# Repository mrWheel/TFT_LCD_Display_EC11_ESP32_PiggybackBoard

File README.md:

# TFT-LCD-Display-EC11 Piggy Back Board

## SoC
This Piggy Back Board uses an **ESP32-S3 SoC**

The board revision is Rev 3.1

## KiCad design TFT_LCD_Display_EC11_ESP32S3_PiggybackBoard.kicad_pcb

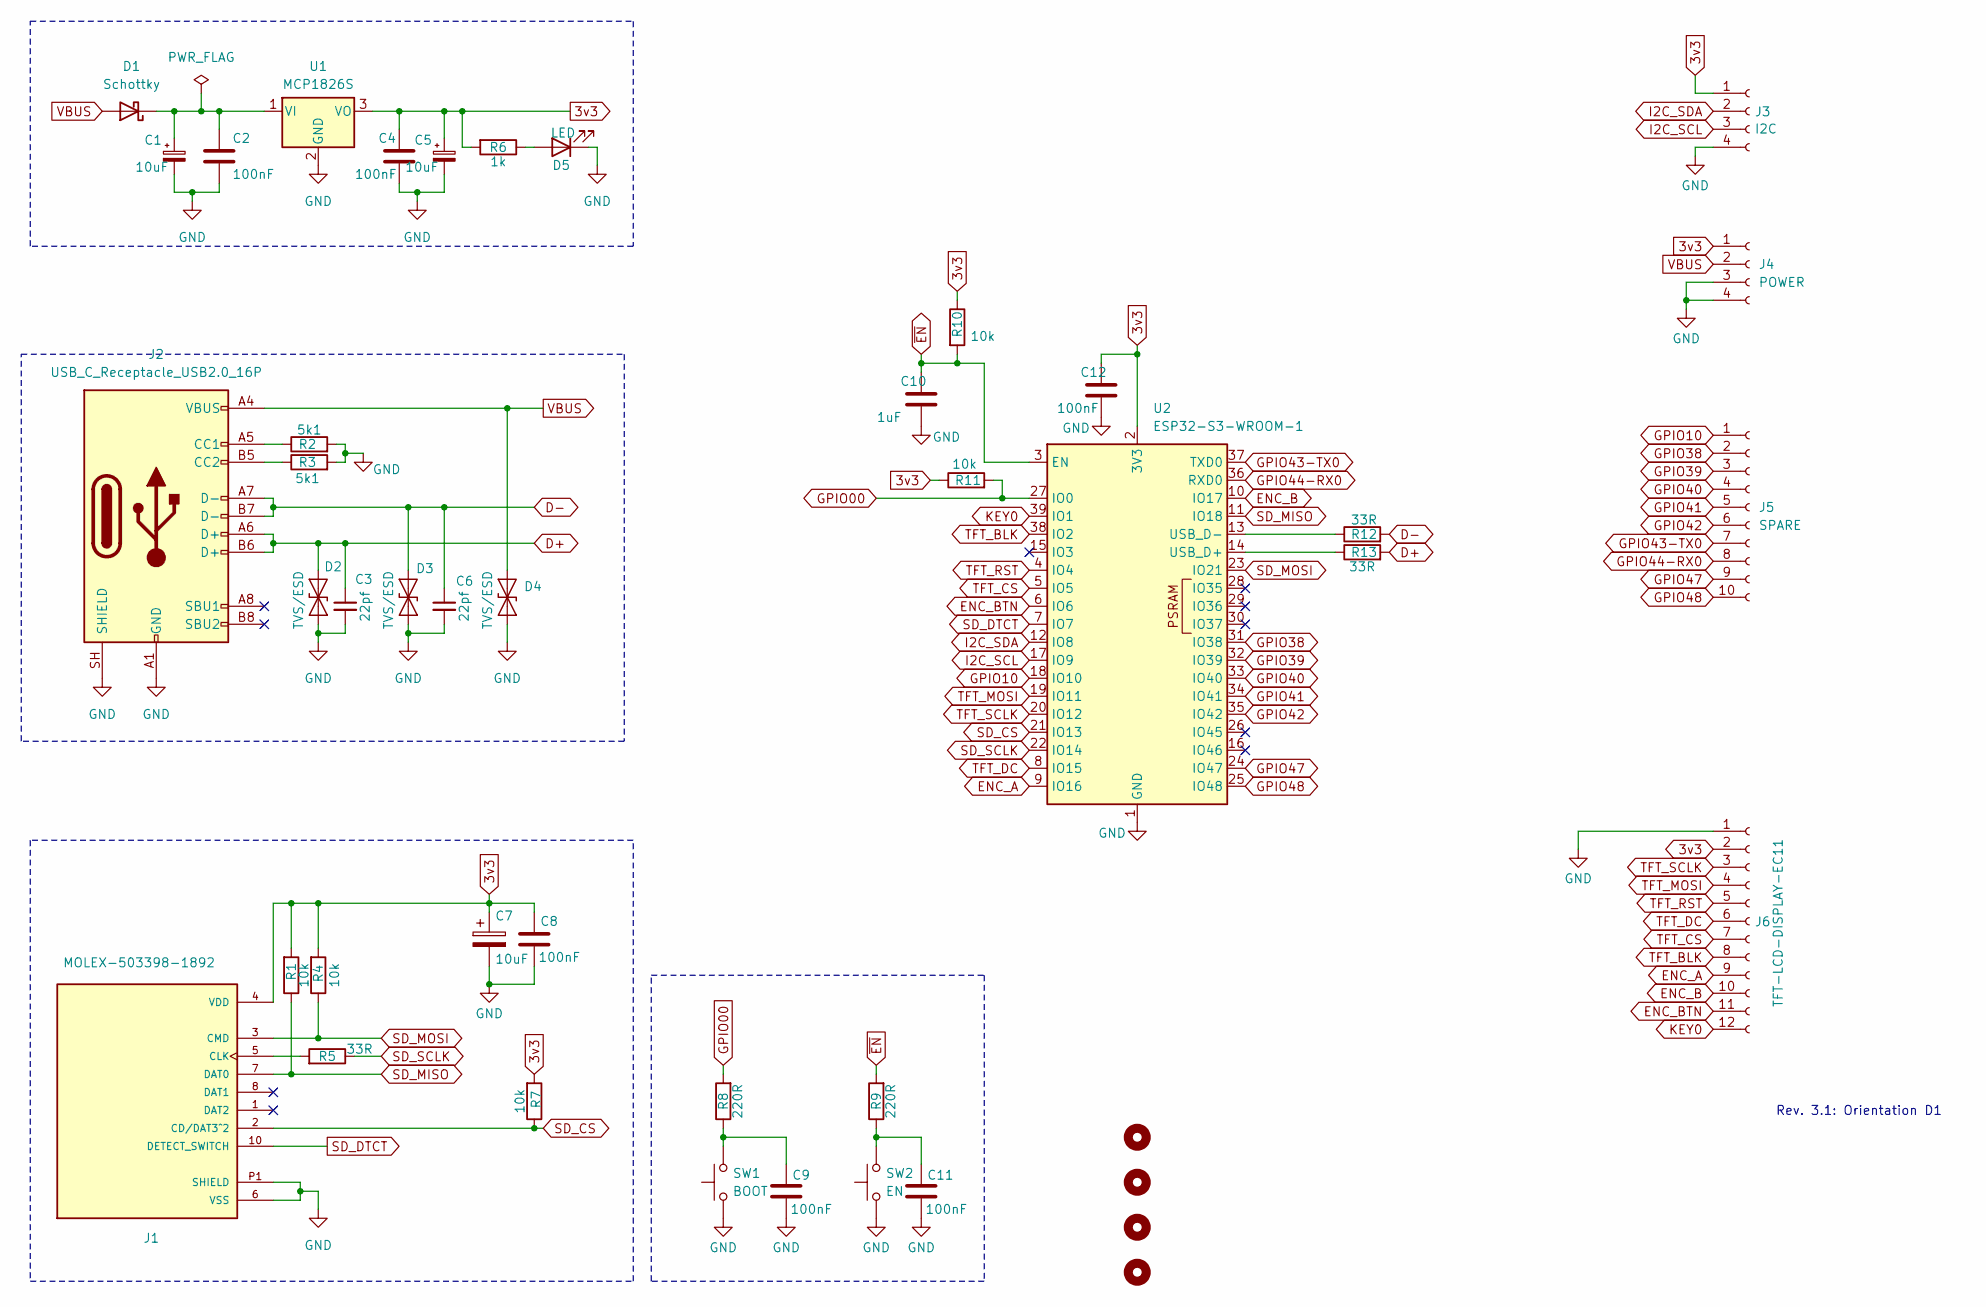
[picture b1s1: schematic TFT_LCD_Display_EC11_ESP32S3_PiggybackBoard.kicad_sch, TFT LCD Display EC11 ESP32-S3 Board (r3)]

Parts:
C1, C5: 10uF; CP_EIA-3216-18_Kemet-A_HandSolder
C2, C4, C8, C9, C11, C12: 100nF; C_1206_3216Metric_Pad1.33x1.80mm_HandSolder
C3, C6: 22pf; C_1206_3216Metric_Pad1.33x1.80mm_HandSolder
C7: 10uF; CP_EIA-7343-31_Kemet-D_HandSolder
C10: 1uF; C_1206_3216Metric_Pad1.33x1.80mm_HandSolder
D1: Schottky; D_SMA_Handsoldering
D2, D3, D4: TVS/ESD; D_SOD-123F
D5: LED; LED_1206_3216Metric_Pad1.42x1.75mm_HandSolder
H1, H2, H3, H4: MountingHole; MountingHole_3.2mm_M3_DIN965_Pad
J1: MOLEX-503398-1892; MOLEX_503398-1892_mod; PARTREV 0
J2: USB_C_Receptacle_USB2.0_16P; USB_C_Receptacle_GCT_USB4085
J3: I2C; PinSocket_1x04_P2.54mm_Vertical
J4: POWER; PinSocket_1x04_P2.54mm_Vertical
J5: SPARE; PinSocket_1x10_P2.54mm_Vertical
J6: TFT-LCD-DISPLAY-EC11; PinHeader_1x12_P2.54mm_Vertical
R1, R4, R7, R10, R11: 10k; R_1206_3216Metric_Pad1.30x1.75mm_HandSolder
R2, R3: 5k1; R_1206_3216Metric_Pad1.30x1.75mm_HandSolder
R5, R12, R13: 33R; R_1206_3216Metric_Pad1.30x1.75mm_HandSolder
R6: 1k; R_1206_3216Metric_Pad1.30x1.75mm_HandSolder
R8, R9: 220R; R_1206_3216Metric_Pad1.30x1.75mm_HandSolder
SW1: BOOT; SW_SPST_FSMSM
SW2: EN; SW_SPST_FSMSM
U1: MCP1826S; SOT-223-3_TabPin2
U2: ESP32-S3-WROOM-1

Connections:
3v3: C4.1, C5.1, C7.1, C8.1, C12.1, J1.4 (VDD), J3.1, J4.1, J6.2, R1.2, R4.2, R6.2, R7.2, R10.1, R11.1, U1.3 (VO), U2.2 (3V3)
D+: C3.1, D2.2 (A2), J2.A6 (D+), J2.B6 (D+), R13.2
D-: C6.1, D3.2 (A2), J2.A7 (D-), J2.B7 (D-), R12.2
ENC_A: J6.9, U2.9 (IO16)
ENC_B: J6.10, U2.10 (IO17)
ENC_BTN: J6.11, U2.6 (IO6)
GND: C1.2, C2.2, C3.2, C4.2, C5.2, C6.2, C7.2, C8.2, C9.2, C10.2, C11.2, C12.2, D2.1 (A1), D3.1 (A1), D4.1 (A1), D5.1 (K), J1.6 (VSS), J1.9 (VSS), J1.P1 (SHIELD), J1.P2 (SHIELD), J1.P3 (SHIELD), J1.P4 (SHIELD), J2.A1 (GND), J2.A12 (GND), J2.B1 (GND), J2.B12 (GND), J2.SH (SHIELD), J3.4, J4.3, J4.4, J6.1, R2.2, R3.2, SW1.1, SW2.1, U1.2 (GND), U2.1 (GND), U2.40 (GND), U2.41 (GND)
GPIO00: R8.2, R11.2, U2.27 (IO0)
GPIO10: J5.1, U2.18 (IO10)
GPIO38: J5.2, U2.31 (IO38)
GPIO39: J5.3, U2.32 (IO39)
GPIO40: J5.4, U2.33 (IO40)
GPIO41: J5.5, U2.34 (IO41)
GPIO42: J5.6, U2.35 (IO42)
GPIO43-TX0: J5.7, U2.37 (TXD0)
GPIO44-RX0: J5.8, U2.36 (RXD0)
GPIO47: J5.9, U2.24 (IO47)
GPIO48: J5.10, U2.25 (IO48)
I2C_SCL: J3.3, U2.17 (IO9)
I2C_SDA: J3.2, U2.12 (IO8)
KEY0: J6.12, U2.39 (IO1)
unnamed: C9.1, R8.1, SW1.2
unnamed: C11.1, R9.1, SW2.2
unnamed: C1.1, C2.1, D1.1 (K), U1.1 (VI)
unnamed: D5.2 (A), R6.1
unnamed: J1.5 (CLK), R5.2
unnamed: J2.A5 (CC1), R2.1
unnamed: J2.B5 (CC2), R3.1
unnamed: R13.1, U2.14 (USB_D+)
unnamed: R12.1, U2.13 (USB_D-)
SD_CS: J1.2 (CD/DAT3^2), R7.1, U2.21 (IO13)
SD_DTCT: J1.10 (DETECT_SWITCH), U2.7 (IO7)
SD_MISO: J1.7 (DAT0), R1.1, U2.11 (IO18)
SD_MOSI: J1.3 (CMD), R4.1, U2.23 (IO21)
SD_SCLK: R5.1, U2.22 (IO14)
TFT_BLK: J6.8, U2.38 (IO2)
TFT_CS: J6.7, U2.5 (IO5)
TFT_DC: J6.6, U2.8 (IO15)
TFT_MOSI: J6.4, U2.19 (IO11)
TFT_RST: J6.5, U2.4 (IO4)
TFT_SCLK: J6.3, U2.20 (IO12)
VBUS: D1.2 (A), D4.2 (A2), J2.A4 (VBUS), J2.A9 (VBUS), J2.B4 (VBUS), J2.B9 (VBUS), J4.2
~EN: C10.1, R9.2, R10.2, U2.3 (EN)

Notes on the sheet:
Rev. 3.1: Orientation D1

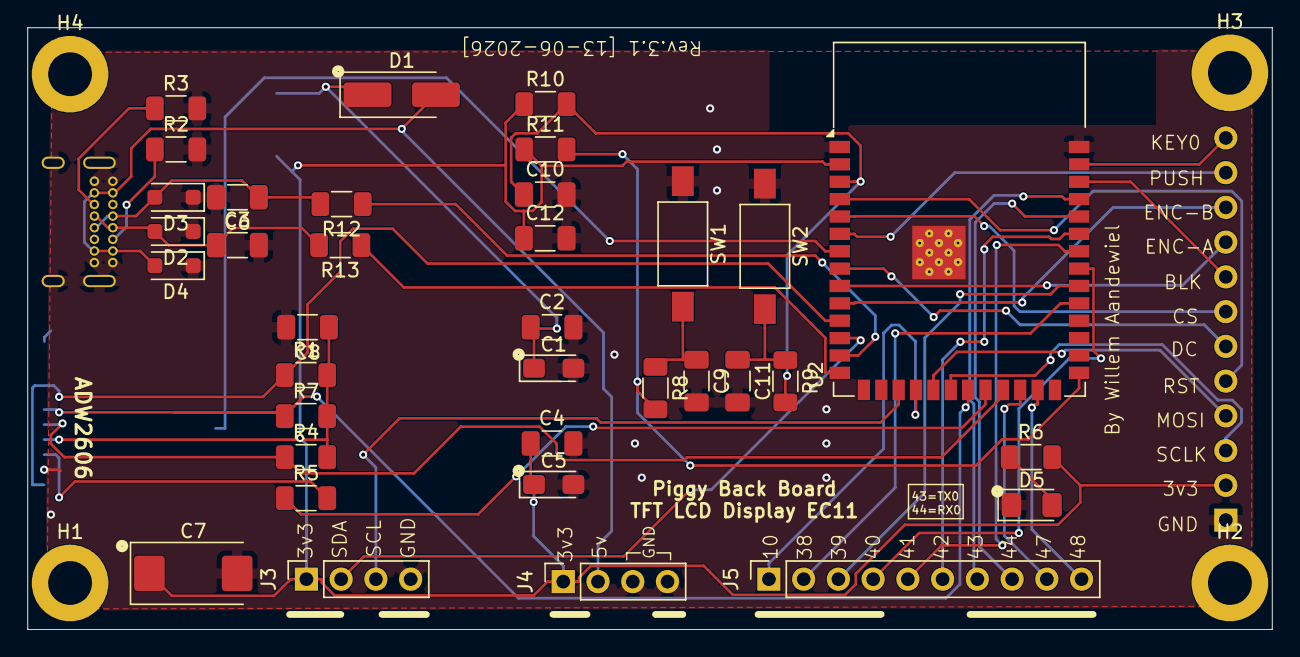
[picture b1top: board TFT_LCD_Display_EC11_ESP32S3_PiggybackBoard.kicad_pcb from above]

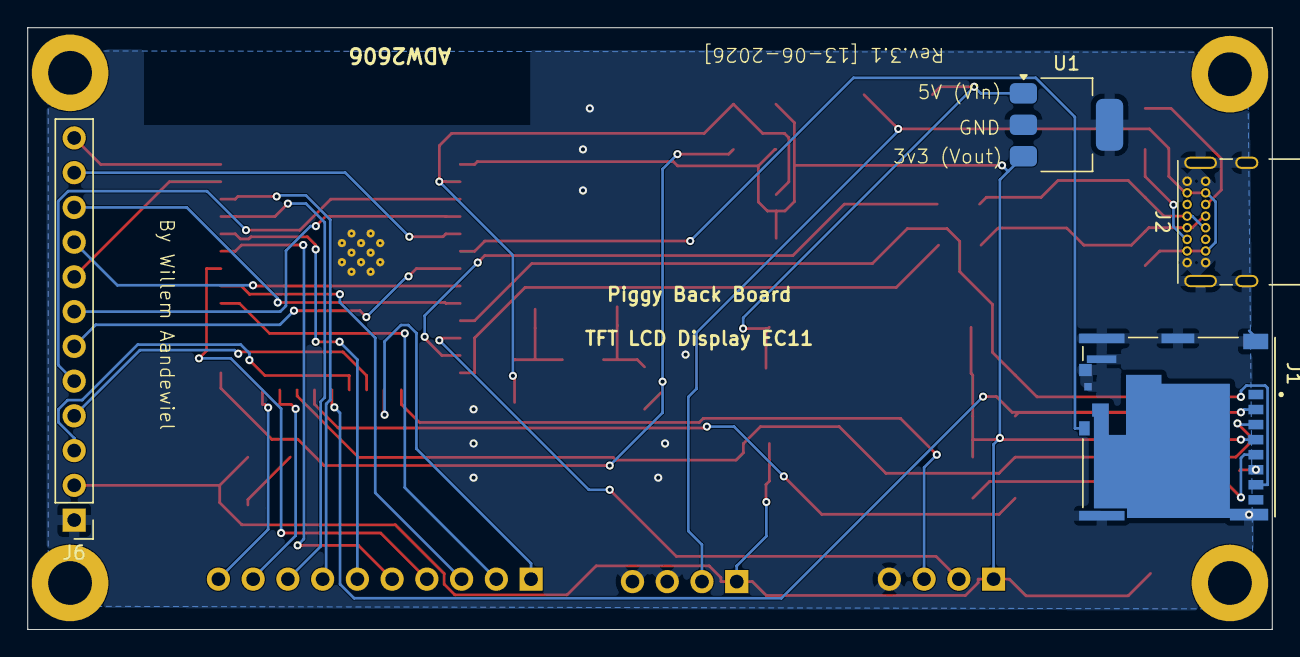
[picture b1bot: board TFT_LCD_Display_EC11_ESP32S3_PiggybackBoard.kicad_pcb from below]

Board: 2 copper layers, 91.0 x 44.0 mm, 44 parts (4 on the bottom side), 43 nets.

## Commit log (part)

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2026-05-18 Refresh index.html with attractive light-themed GUI
    Agent-Logs-Url: https://github.com/mrWheel/TFT_LCD_Display_EC11_Board/sessions/47a6cf73-9775-4ba0-a26b-c24326022f75
